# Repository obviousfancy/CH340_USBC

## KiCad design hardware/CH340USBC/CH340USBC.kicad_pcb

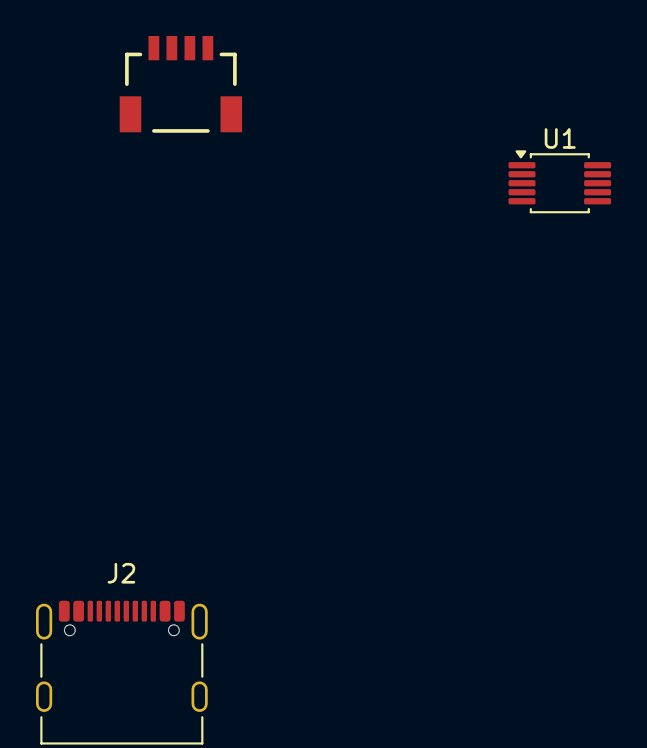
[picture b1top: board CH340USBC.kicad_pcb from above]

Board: 2 copper layers, 3 parts (0 on the bottom side), 2 nets, no tracks yet.

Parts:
J1: Qwiic_RA; JST_1x04_P1.0mm_Horizontal_SMD
J2: USB_C_Receptacle_USB2.0_16P; USB_C_Receptacle_Palconn_UTC16-G
U1: CH340E; MSOP-10_3x3mm_P0.5mm

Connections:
unnamed: J2.A1 (GND), J2.A12 (GND), J2.B1 (GND), J2.B12 (GND)
unnamed: J2.A4 (VBUS), J2.A9 (VBUS), J2.B4 (VBUS), J2.B9 (VBUS)

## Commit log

2026-05-13 feat: update hardware files for the USBCH340 with USB C
2026-05-13 feat: update schematic
